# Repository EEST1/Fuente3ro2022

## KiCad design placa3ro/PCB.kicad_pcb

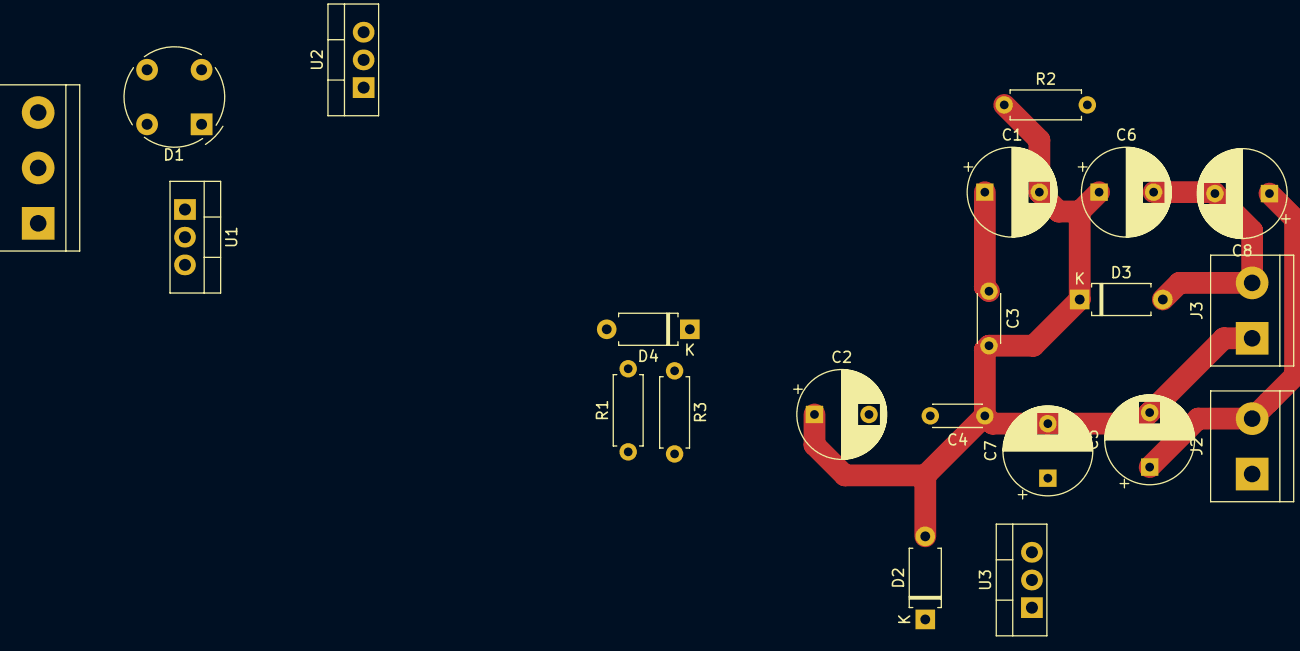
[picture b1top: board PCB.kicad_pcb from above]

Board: 2 copper layers, 21 parts (0 on the bottom side), 8 nets.

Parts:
C1, C2, C5, C6, C7, C8: CP1; CP_Radial_D8.0mm_P5.00mm
C3, C4: C; C_Disc_D4.3mm_W1.9mm_P5.00mm
D1: W10G; Diode_Bridge_Round_D9.0mm
D2, D3, D4: D; D_A-405_P7.62mm_Horizontal
J1: Screw_Terminal_01x03; TerminalBlock_bornier-3_P5.08mm
J2, J3: Screw_Terminal_01x02; TerminalBlock_bornier-2_P5.08mm
R1, R2, R3: R; R_Axial_DIN0207_L6.3mm_D2.5mm_P7.62mm_Horizontal
U1: L7812; TO-220-3_Vertical
U2: L7912; TO-220-3_Vertical
U3: L7805; TO-220-3_Vertical

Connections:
Earth: C1.2, C2.1, C3.2, C4.1, C5.2, C6.1, C7.2, D2.2, D3.1, D4.2, J1.1, J3.1, R1.2, R2.1, R3.2, U1.2, U2.1, U3.2
unnamed: C1.1, C3.1, D1.1, U1.1
unnamed: C2.2, C4.2, D1.3, U2.2
unnamed: C5.1, C8.1, D2.1, J2.2, R1.1, U1.3, U3.1
unnamed: C6.2, C8.2, D3.2, J3.2, R2.2, U2.3
unnamed: C7.1, D4.1, J2.1, R3.1, U3.3
unnamed: D1.2, J1.3
unnamed: D1.4, J1.2
